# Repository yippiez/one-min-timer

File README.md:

# one-min-timer
basic one shot one minute timer module

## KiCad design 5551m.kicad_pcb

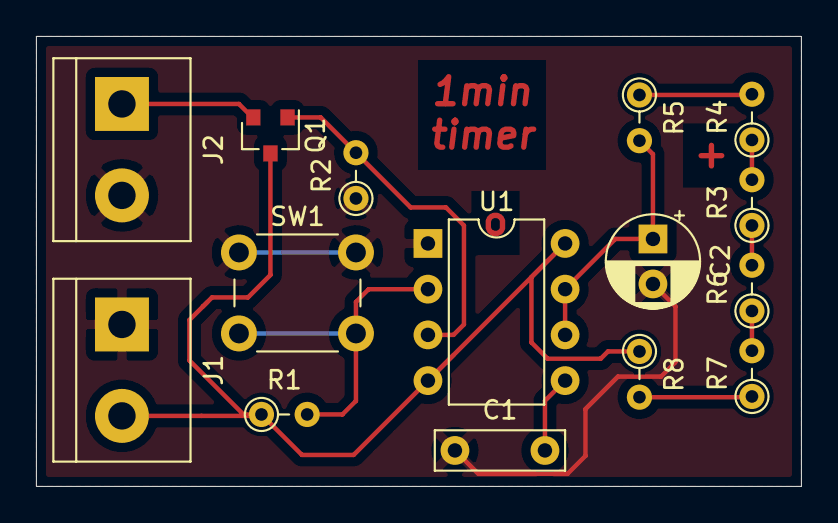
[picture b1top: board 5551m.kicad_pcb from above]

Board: 2 copper layers, 42.5 x 25.0 mm, 15 parts (0 on the bottom side), 12 nets.

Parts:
C1: 0.1uf; C_Rect_L7.0mm_W2.0mm_P5.00mm
C2: 100uf; CP_Radial_D5.0mm_P2.50mm
J1, J2: Screw_Terminal_01x02; TerminalBlock_bornier-2_P5.08mm
Q1: 2N7002H; SOT-23
R1, R2: 10k; R_Axial_DIN0204_L3.6mm_D1.6mm_P2.54mm_Vertical
R3, R4, R5, R6, R7, R8: 100k; R_Axial_DIN0204_L3.6mm_D1.6mm_P2.54mm_Vertical
SW1: SW_Push; SW_PUSH_6mm_H4.3mm
U1: LM555xN; DIP-8_W7.62mm

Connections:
GND: C1.1, C2.2, J1.1, J2.2, R2.1, SW1.1, U1.1
unnamed: C1.2, U1.5
unnamed: C2.1, R5.2, U1.6, U1.7
unnamed: J2.1, Q1.2
unnamed: Q1.1, R2.2, U1.3
unnamed: R1.2, SW1.2, U1.2
unnamed: R3.1, R6.2
unnamed: R3.2, R4.1
unnamed: R4.2, R5.1
unnamed: R6.1, R7.2
unnamed: R7.1, R8.2
VCC: J1.2, Q1.3, R1.1, R8.1, U1.4, U1.8
